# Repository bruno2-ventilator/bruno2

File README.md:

# BrunO2 Open Source Ventilator
This repository contains design information for a low cost ventilator designed by a team based at Brown University. We are a group of engineers, medical practitioners, and device designers developing a ventilator system based around custom proportional valves, MEMS pressure sensors, and closed-loop control system.

More details and videos are available on the [BrunO2 website](https://sites.brown.edu/bruno2/).

---
## License
These open source ventilator design materials are provided under the conditions specified in the [Permissive License](Permissive%20License--Brown%20University%20041720.pdf)

---
## Quick Links:
[System](Design%20Materials/System/)   /   [Mechanical](Design%20Materials/Mechanical/)   /   [Software](Design%20Materials/Software/)   /   [Electronics](Design%20Materials/Electronics/)   /   [BrunO2 website](https://sites.brown.edu/bruno2/).

---
## Getting Started:

COMING SOON

---
# Contributors to the BrunO2 project include:

**Brown University School of Engineering:**
- Prof. Dan Harris (Fluids)
- Prof. Roberto Zenit (Fluids)
- Prof. Kenny Breuer (Fluids)
- Prof. Jacob Rosenstein (ECE)
- Chris Bull (Director of BDW)
- Ben Lyons (BDW Staff)
- Garam Lee (MechE)
- Ian Ho (MechE)
- John Antolik (MechE)
- Will Haddock (MechE)
- Jacob Morse (MechE)
- Alberto Bortoni (ECE)
- Marc Powell (BME)
- Eli Silver (MechE)
- Chris Arcadia (ECE)

**Medical team and advisors:**
- Farah L Laiwalla MD/PhD, Prof, Brown BME
- Dan Dworkis, MD/PhD., Asst. Prof. Emergency Medicine, Keck School of Medicine of USC
- Gerardo P. Carino MD/PhD., Associate Professor of Medicine (Clinical), ICU Director, The Miriam Hospital
- Nicole Thomasian, Brown med student
- Roja Garimella, Brown med student
- Anastassia Gorvitovskaia, Brown med student

**Practicing Engineers:**
- Dave Durfee (Bay Computer Associates, Inc.)
- Andy Leonczyk (Ximedica)

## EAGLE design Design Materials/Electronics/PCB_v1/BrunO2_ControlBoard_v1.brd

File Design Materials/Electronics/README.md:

# BrunO2 Ventilator Electronic Hardware Components

---
These open source ventilator design materials are provided under the conditions specified in the [Permissive License](../../Permissive%20License--Brown%20University%20041720.pdf)

---
# MORE DETAILS COMING SOON

---
# BrunO2 PCB v1
## 

[PDF Schematic](PCB_v1/BrunO2%20PCB%20Schematic%20v1.pdf)

[Eagle Schematic](PCB_v1/BrunO2_ControlBoard_v1.sch)

[Eagle Layout](PCB_v1/BrunO2_ControlBoard_v1.brd)

[Gerber Files](PCB_v1/BrunO2_ControlBoard_v1_Gerbers_2020-04-05.zip)

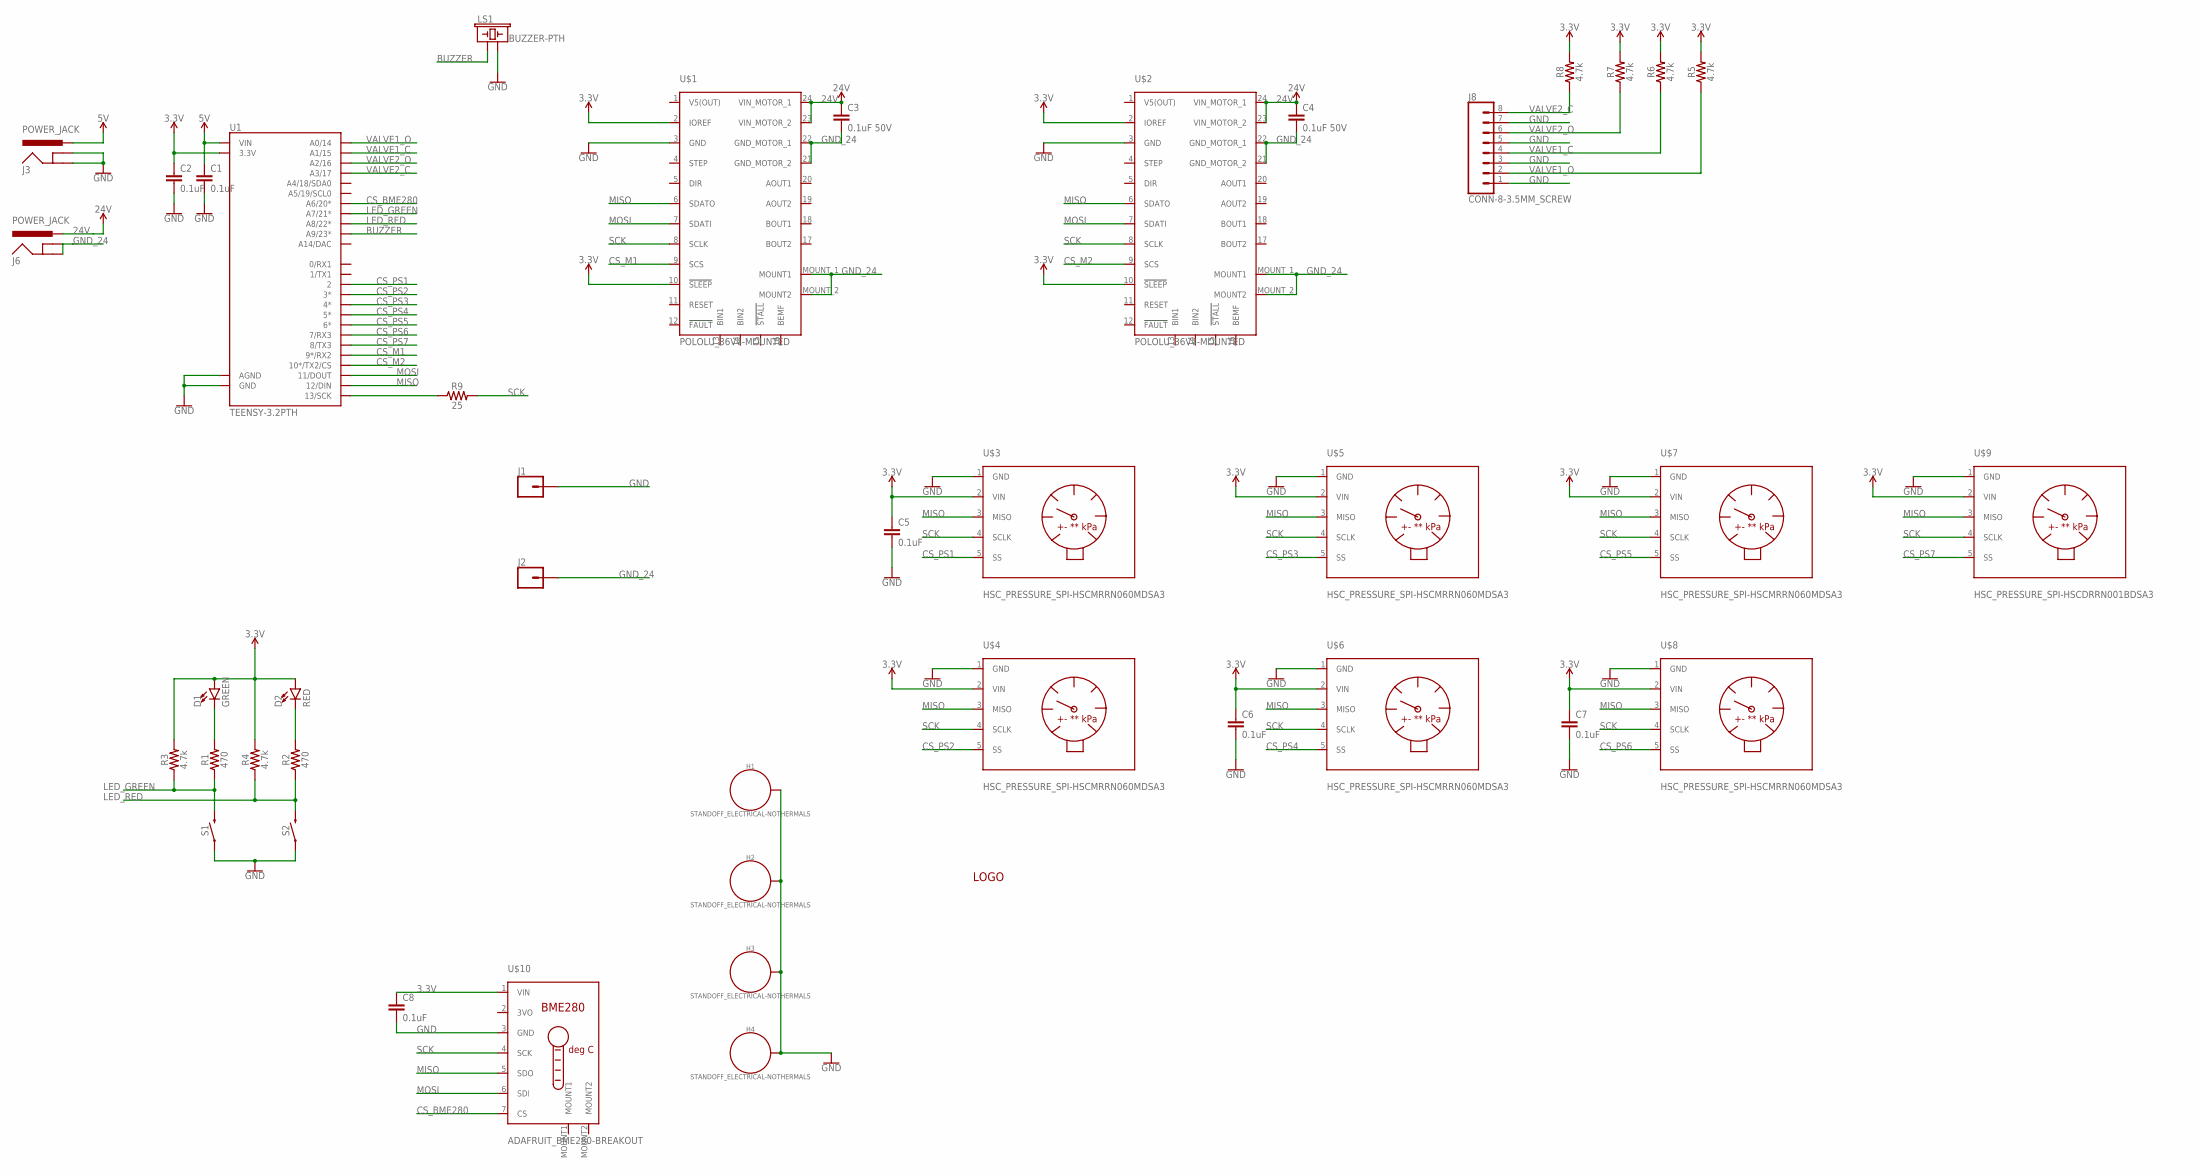
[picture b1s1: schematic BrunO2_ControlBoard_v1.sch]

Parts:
C1, C2, C5, C6, C7, C8: 0.1uF; CAP-PTH-SMALL-KIT
C3, C4: 0.1uF 50V; CAP-PTH-SMALL-KIT
D1: GREEN; LED_5MM-KIT-NO-SILK
D2: RED; LED_5MM-KIT-NO-SILK
H1, H2, H3, H4: STANDOFF_ELECTRICAL-NOTHERMALS; STANDOFF-ELECTRICAL-NOTHERMALS
J1, J2: CONN_01; 1X01
J3, J6: POWER_JACK; POWER_JACK_PTH
J8: CONN-8-3.5MM_SCREW; SCREWTERMINAL-3.5MM-8
LS1: BUZZER-PTH; BUZZER-12MM
R1, R2: 470; AXIAL-0.3
R3, R4, R5, R6, R7, R8: 4.7k; AXIAL-0.3
R9: 25; AXIAL-0.3
S1, S2: MOMENTARY-SWITCH-SPST-PTH-6.0MM; TACTILE_SWITCH_PTH_6.0MM
U1: TEENSY-3.2PTH; TEENSY_TEENSY-3.2-PTH
U$1, U$2: POLOLU_36V4-MOUNTED; POLOLU_36V4
U$3, U$4, U$5, U$6, U$7, U$8: HSC_PRESSURE_SPI-HSCMRRN060MDSA3; HSC_PRESSURE_DIP
U$9: HSC_PRESSURE_SPI-HSCDRRN001BDSA3; HSC_PRESSURE_DIP
U$10: ADAFRUIT_BME280-BREAKOUT; ADAFRUIT_BME280
U$11: LOGO-BRUNO2; BRUNO2_LOGO

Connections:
3.3V: C2.1, C5.1, C6.1, C7.1, C8.1, D1.A, D2.A, R3.P$2 (2), R4.P$2 (2), R5.P$2 (2), R6.P$2 (2), R7.P$2 (2), R8.P$2 (2), U1.3.3V, U1.3.3V-1 (3.3V), U$1.2 (IOREF), U$1.10 (!SLEEP), U$2.2 (IOREF), U$2.10 (!SLEEP), U$3.2 (VIN), U$4.2 (VIN), U$5.2 (VIN), U$6.2 (VIN), U$7.2 (VIN), U$8.2 (VIN), U$9.2 (VIN), U$10.1 (VIN)
5V: C1.1, J3.PWR, U1.VIN
24V: C3.1, C4.1, J6.PWR, U$1.23 (VIN_MOTOR_2), U$1.24 (VIN_MOTOR_1), U$2.23 (VIN_MOTOR_2), U$2.24 (VIN_MOTOR_1)
BUZZER: LS1.+ (1), U1.23 (A9/23*)
CS_BME280: U1.20 (A6/20*), U$10.7 (CS)
CS_M1: U1.9 (9*/RX2), U$1.9 (SCS)
CS_M2: U1.10 (10*/TX2/CS), U$2.9 (SCS)
CS_PS1: U1.2, U$3.5 (SS)
CS_PS2: U1.3 (3*), U$4.5 (SS)
CS_PS3: U1.4 (4*), U$5.5 (SS)
CS_PS4: U1.5 (5*), U$6.5 (SS)
CS_PS5: U1.6 (6*), U$7.5 (SS)
CS_PS6: U1.7 (7/RX3), U$8.5 (SS)
CS_PS7: U1.8 (8/TX3), U$9.5 (SS)
GND: C1.2, C2.2, C5.2, C6.2, C7.2, C8.2, H1.P1, H2.P1, H3.P1, H4.P1, J1.1, J3.GND, J3.GNDBREAK, J8.1, J8.3, J8.5, J8.7, LS1.- (2), S1.1, S2.1, U1.AGND, U1.GND, U1.GND1 (GND), U$1.3 (GND), U$2.3 (GND), U$3.1 (GND), U$4.1 (GND), U$5.1 (GND), U$6.1 (GND), U$7.1 (GND), U$8.1 (GND), U$9.1 (GND), U$10.3 (GND)
GND_24: C3.2, C4.2, J2.1, J6.GND, J6.GNDBREAK, U$1.21 (GND_MOTOR_2), U$1.22 (GND_MOTOR_1), U$1.MOUNT_1 (MOUNT1), U$1.MOUNT_2 (MOUNT2), U$2.21 (GND_MOTOR_2), U$2.22 (GND_MOTOR_1), U$2.MOUNT_1 (MOUNT1), U$2.MOUNT_2 (MOUNT2)
LED_GREEN: R1.P$1 (1), R3.P$1 (1), S1.3 (2), U1.21 (A7/21*)
LED_RED: R2.P$1 (1), R4.P$1 (1), S2.3 (2), U1.22 (A8/22*)
MISO: U1.12 (12/DIN), U$1.6 (SDATO), U$2.6 (SDATO), U$3.3 (MISO), U$4.3 (MISO), U$5.3 (MISO), U$6.3 (MISO), U$7.3 (MISO), U$8.3 (MISO), U$9.3 (MISO), U$10.5 (SDO)
MOSI: U1.11 (11/DOUT), U$1.7 (SDATI), U$2.7 (SDATI), U$10.6 (SDI)
unnamed: D1.K (C), R1.P$2 (2)
unnamed: R9.P$1 (1), U1.13 (13/SCK)
unnamed: D2.K (C), R2.P$2 (2)
SCK: R9.P$2 (2), U$1.8 (SCLK), U$2.8 (SCLK), U$3.4 (SCLK), U$4.4 (SCLK), U$5.4 (SCLK), U$6.4 (SCLK), U$7.4 (SCLK), U$8.4 (SCLK), U$9.4 (SCLK), U$10.4 (SCK)
VALVE1_C: J8.4, R6.P$1 (1), U1.15 (A1/15)
VALVE1_O: J8.2, R5.P$1 (1), U1.14 (A0/14)
VALVE2_C: J8.8, R8.P$1 (1), U1.17 (A3/17)
VALVE2_O: J8.6, R7.P$1 (1), U1.16 (A2/16)

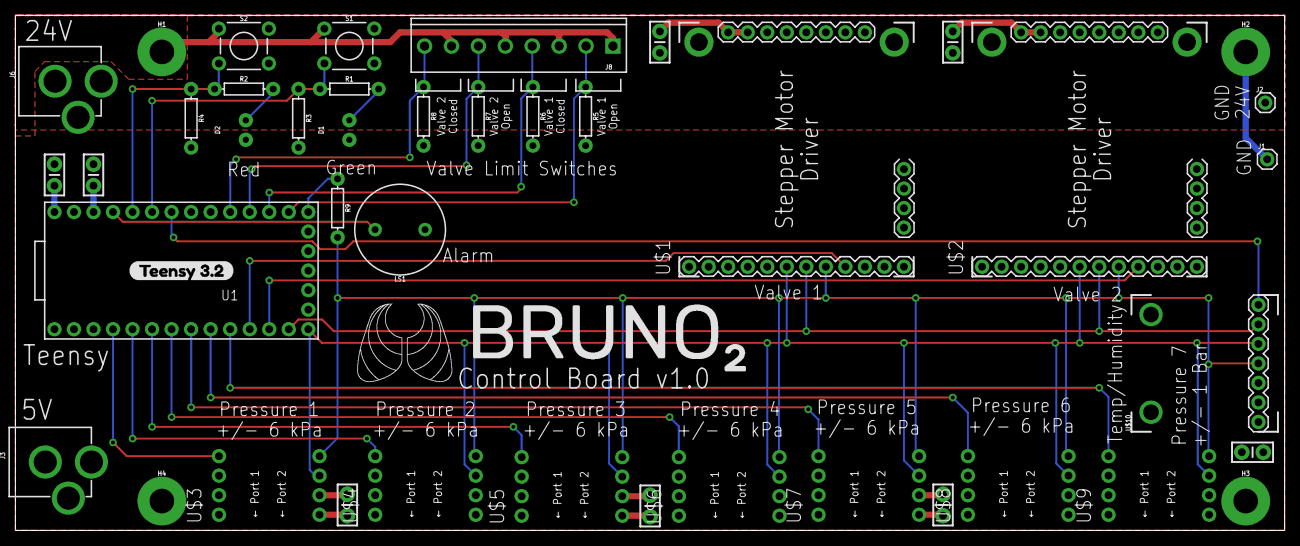
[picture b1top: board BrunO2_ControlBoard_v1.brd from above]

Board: 2 copper layers, 165.1 x 67.0 mm, 43 parts (0 on the bottom side), 28 nets.

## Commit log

2020-03-26 raspi dir
2020-03-29 initial ui, non-functional
2020-03-29 All messages between Pi + Teensy should work; however they are not acknowledged.
2020-03-29 C:/Program Files/Git/c, /s, /p, /m messages are all handled/sent. /e,/c,/b are ignored. Recieved messages are acknowledged, but no acknowledgements are expected on sent messages. main_basic.py now ta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
2020-03-30 Added selection cycling using + - keys
2020-03-30 ui change
2020-03-31 Fixed communication bug
2020-03-31 formatting
2020-03-31 almost done
2020-03-31 Added initial settings and timeout between first messages
2020-03-31 more
2020-04-05 added submodules:
2020-04-05 before new submodule
2020-04-05 removing submodule, arduino includes sucks
2020-04-08 before branch
2020-04-09 readme instructions
2020-04-10 raspi/raspi-setup.md
2020-04-13 splash screen
2020-04-14 testing on pi
2020-04-14 raspi installation instructions
2020-04-14 renamed readme file
2020-04-17 basic functionality, open loop
2020-04-17 first commit to org
2020-04-17 Set theme jekyll-theme-minimal
2020-04-18 new directory structure
2020-04-18 organization
2020-04-18 readme updates
2020-04-18 links
2020-04-18 PCB files
2020-04-18 electronics update
2020-04-18 add venturi design
2020-04-19 Added PDF of design doc, fixed venturi README formatting
2020-04-19 system diagrams
2020-04-19 Adding teensy pin assigments and images of top and bottom of pcb
2020-04-19 cleanup
2020-04-19 added valve design materials
2020-04-19 clean up
2020-04-19 Adapters

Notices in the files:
parts and their libraries:
SparkFun-LED: Licensing: Creative Commons ShareAlike 4.0 International - https://creativecommons.org/licenses/by-sa/4.0
